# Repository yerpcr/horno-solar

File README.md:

# Horno solar
Se crea un sistema de control de temperatura para un sistema de horno solar

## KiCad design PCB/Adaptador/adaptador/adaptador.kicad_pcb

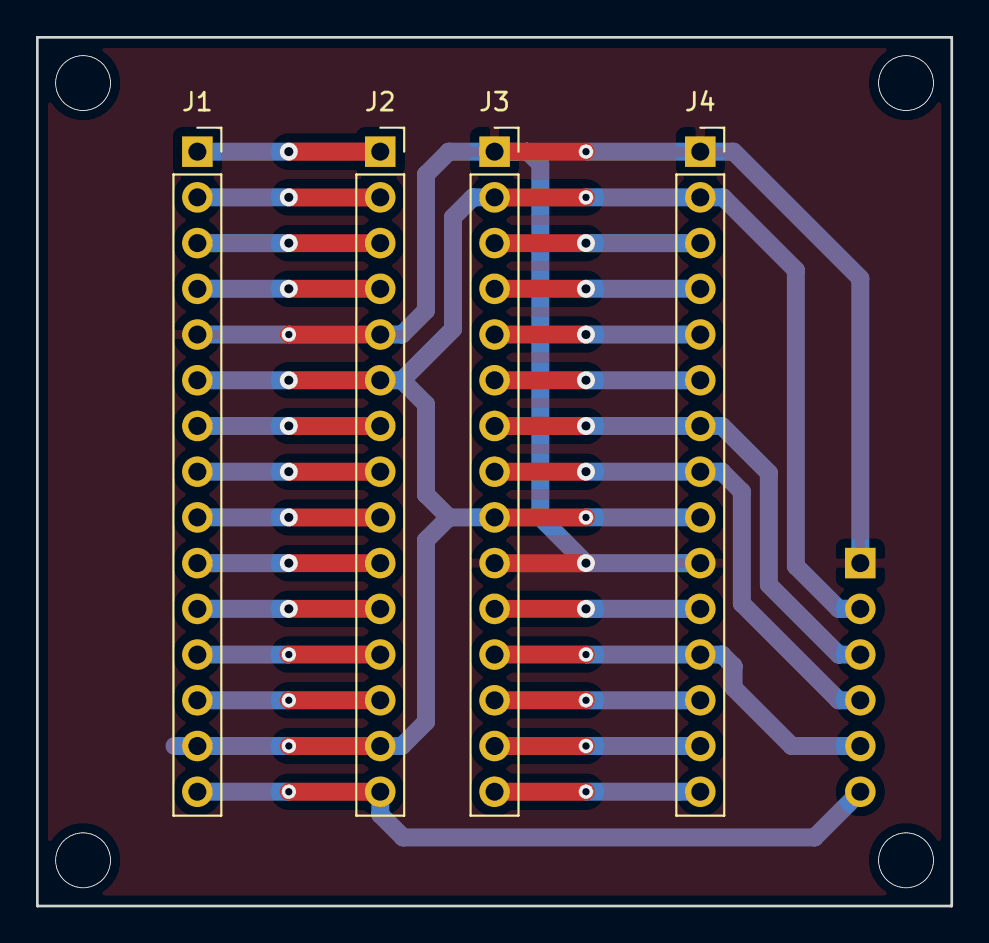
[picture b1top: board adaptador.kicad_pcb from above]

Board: 2 copper layers, 50.8 x 48.3 mm, 5 parts (1 on the bottom side), 25 nets.

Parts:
J1, J4: Conn_01x15_Female; PinSocket_1x15_P2.54mm_Vertical
J2, J3: Conn_01x15_Male; PinSocket_1x15_P2.54mm_Vertical
J5: Conn_01x06_Male; PinSocket_1x06_P2.54mm_Horizontal

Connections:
/Analogo: J1.15, J2.15, J5.6
GND: J1.6, J1.14, J2.6, J2.14, J3.2, J3.9, J4.2, J4.9, J5.2
unnamed: J1.1, J2.1
unnamed: J1.2, J2.2
unnamed: J1.3, J2.3
unnamed: J1.4, J2.4
unnamed: J1.7, J2.7
unnamed: J1.8, J2.8
unnamed: J1.9, J2.9
unnamed: J1.10, J2.10
unnamed: J1.11, J2.11
unnamed: J1.12, J2.12
unnamed: J1.13, J2.13
unnamed: J3.3, J4.3
unnamed: J3.4, J4.4
unnamed: J3.5, J4.5
unnamed: J3.6, J4.6
unnamed: J3.7, J4.7, J5.3
unnamed: J3.8, J4.8, J5.4
unnamed: J3.11, J4.11
unnamed: J3.12, J4.12, J5.5
unnamed: J3.13, J4.13
unnamed: J3.14, J4.14
unnamed: J3.15, J4.15
VCC: J1.5, J2.5, J3.1, J3.10, J4.1, J4.10, J5.1

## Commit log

2021-08-22 Interfaz de adquisicion de datos
2021-08-25 Funcion de conexion a wifi
2021-08-25 Actualizacion gitignore
2021-08-25 Eliminacion de txt
2021-08-25 Lectura de senson y configuracion de timer
2021-08-30 Cambio de resistencia de medicion. R=1.1ohms
2021-09-14 Primeros prototipos de PCB para pruebas de temperatura
